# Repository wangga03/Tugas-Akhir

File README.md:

## Untuk push ke github :
1. $ git add .
2. $ git commit -m "<ini_pesan>"
3. $ git push

## Membuat branch baru (jika perlu)
$ git branch <nama_branch> : 
## pindah branch
$ git checkout <nama_baranch>

## Merge
### Misal kita ingin merge " wgg -> main " :
1. pergi ke main dulu : $ git checkout main
2. baru jalankan : $ git merge wgg
3. kemudian jalankan : $ git push

### Untuk cek sedang berada di branch mana :
$ git status
### kemudian akan muncul output :
On branch main
Your branch is up to date with 'origin/main'.

nothing to commit, working tree clean

berarti sedang berada di branch main

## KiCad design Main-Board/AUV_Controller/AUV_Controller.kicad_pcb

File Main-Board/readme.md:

Berisi tentang board unbtuk AUV
Halo test branch

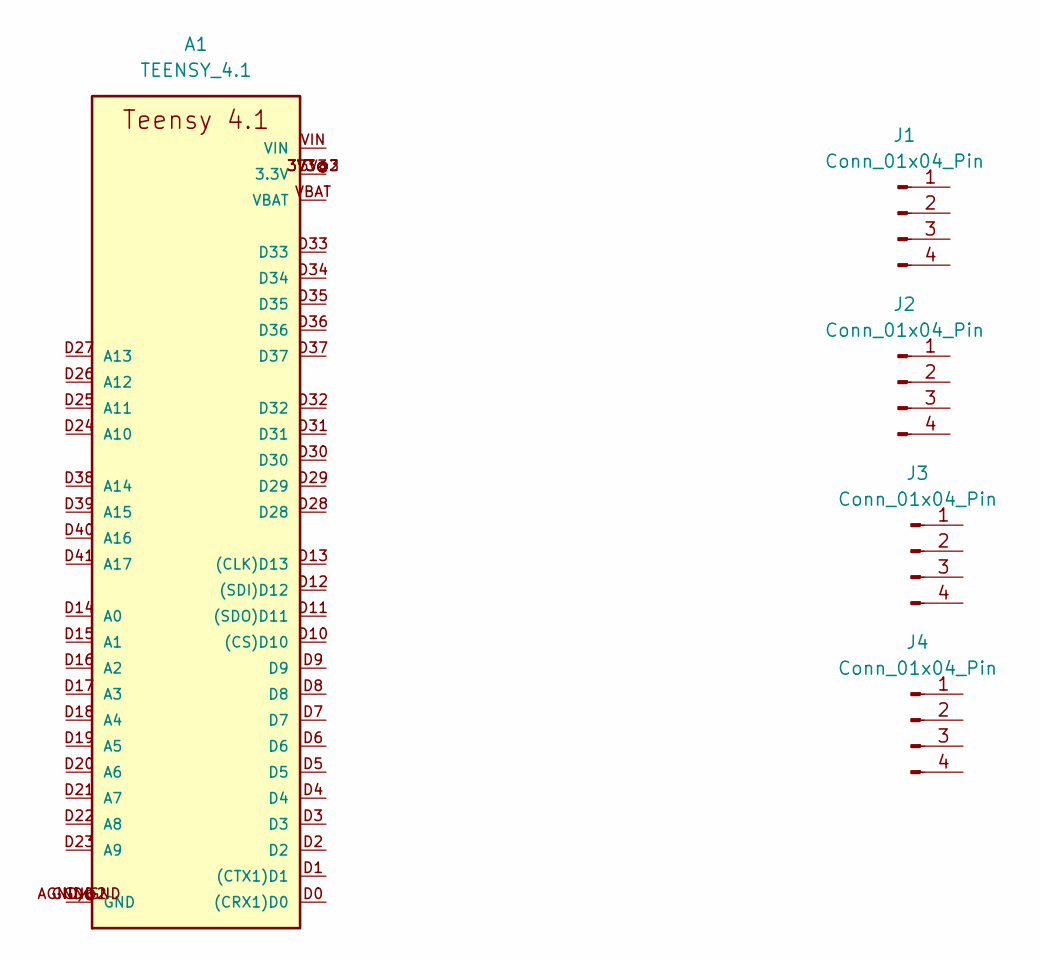
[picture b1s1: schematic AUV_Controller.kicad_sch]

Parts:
A1: TEENSY_4.1; TEENSY_LONG_EXT
J1, J2, J3, J4: Conn_01x04_Pin; JST_EH_S4B-EH_1x04_P2.50mm_Horizontal

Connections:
unnamed: A1.3V3 (3.3V), A1.3V3@2 (3.3V), A1.3V3@3 (3.3V)
unnamed: A1.AGND/GND (GND), A1.GND, A1.GND@2 (GND)

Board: 2 copper layers, 5 parts (0 on the bottom side), 2 nets, no tracks yet.

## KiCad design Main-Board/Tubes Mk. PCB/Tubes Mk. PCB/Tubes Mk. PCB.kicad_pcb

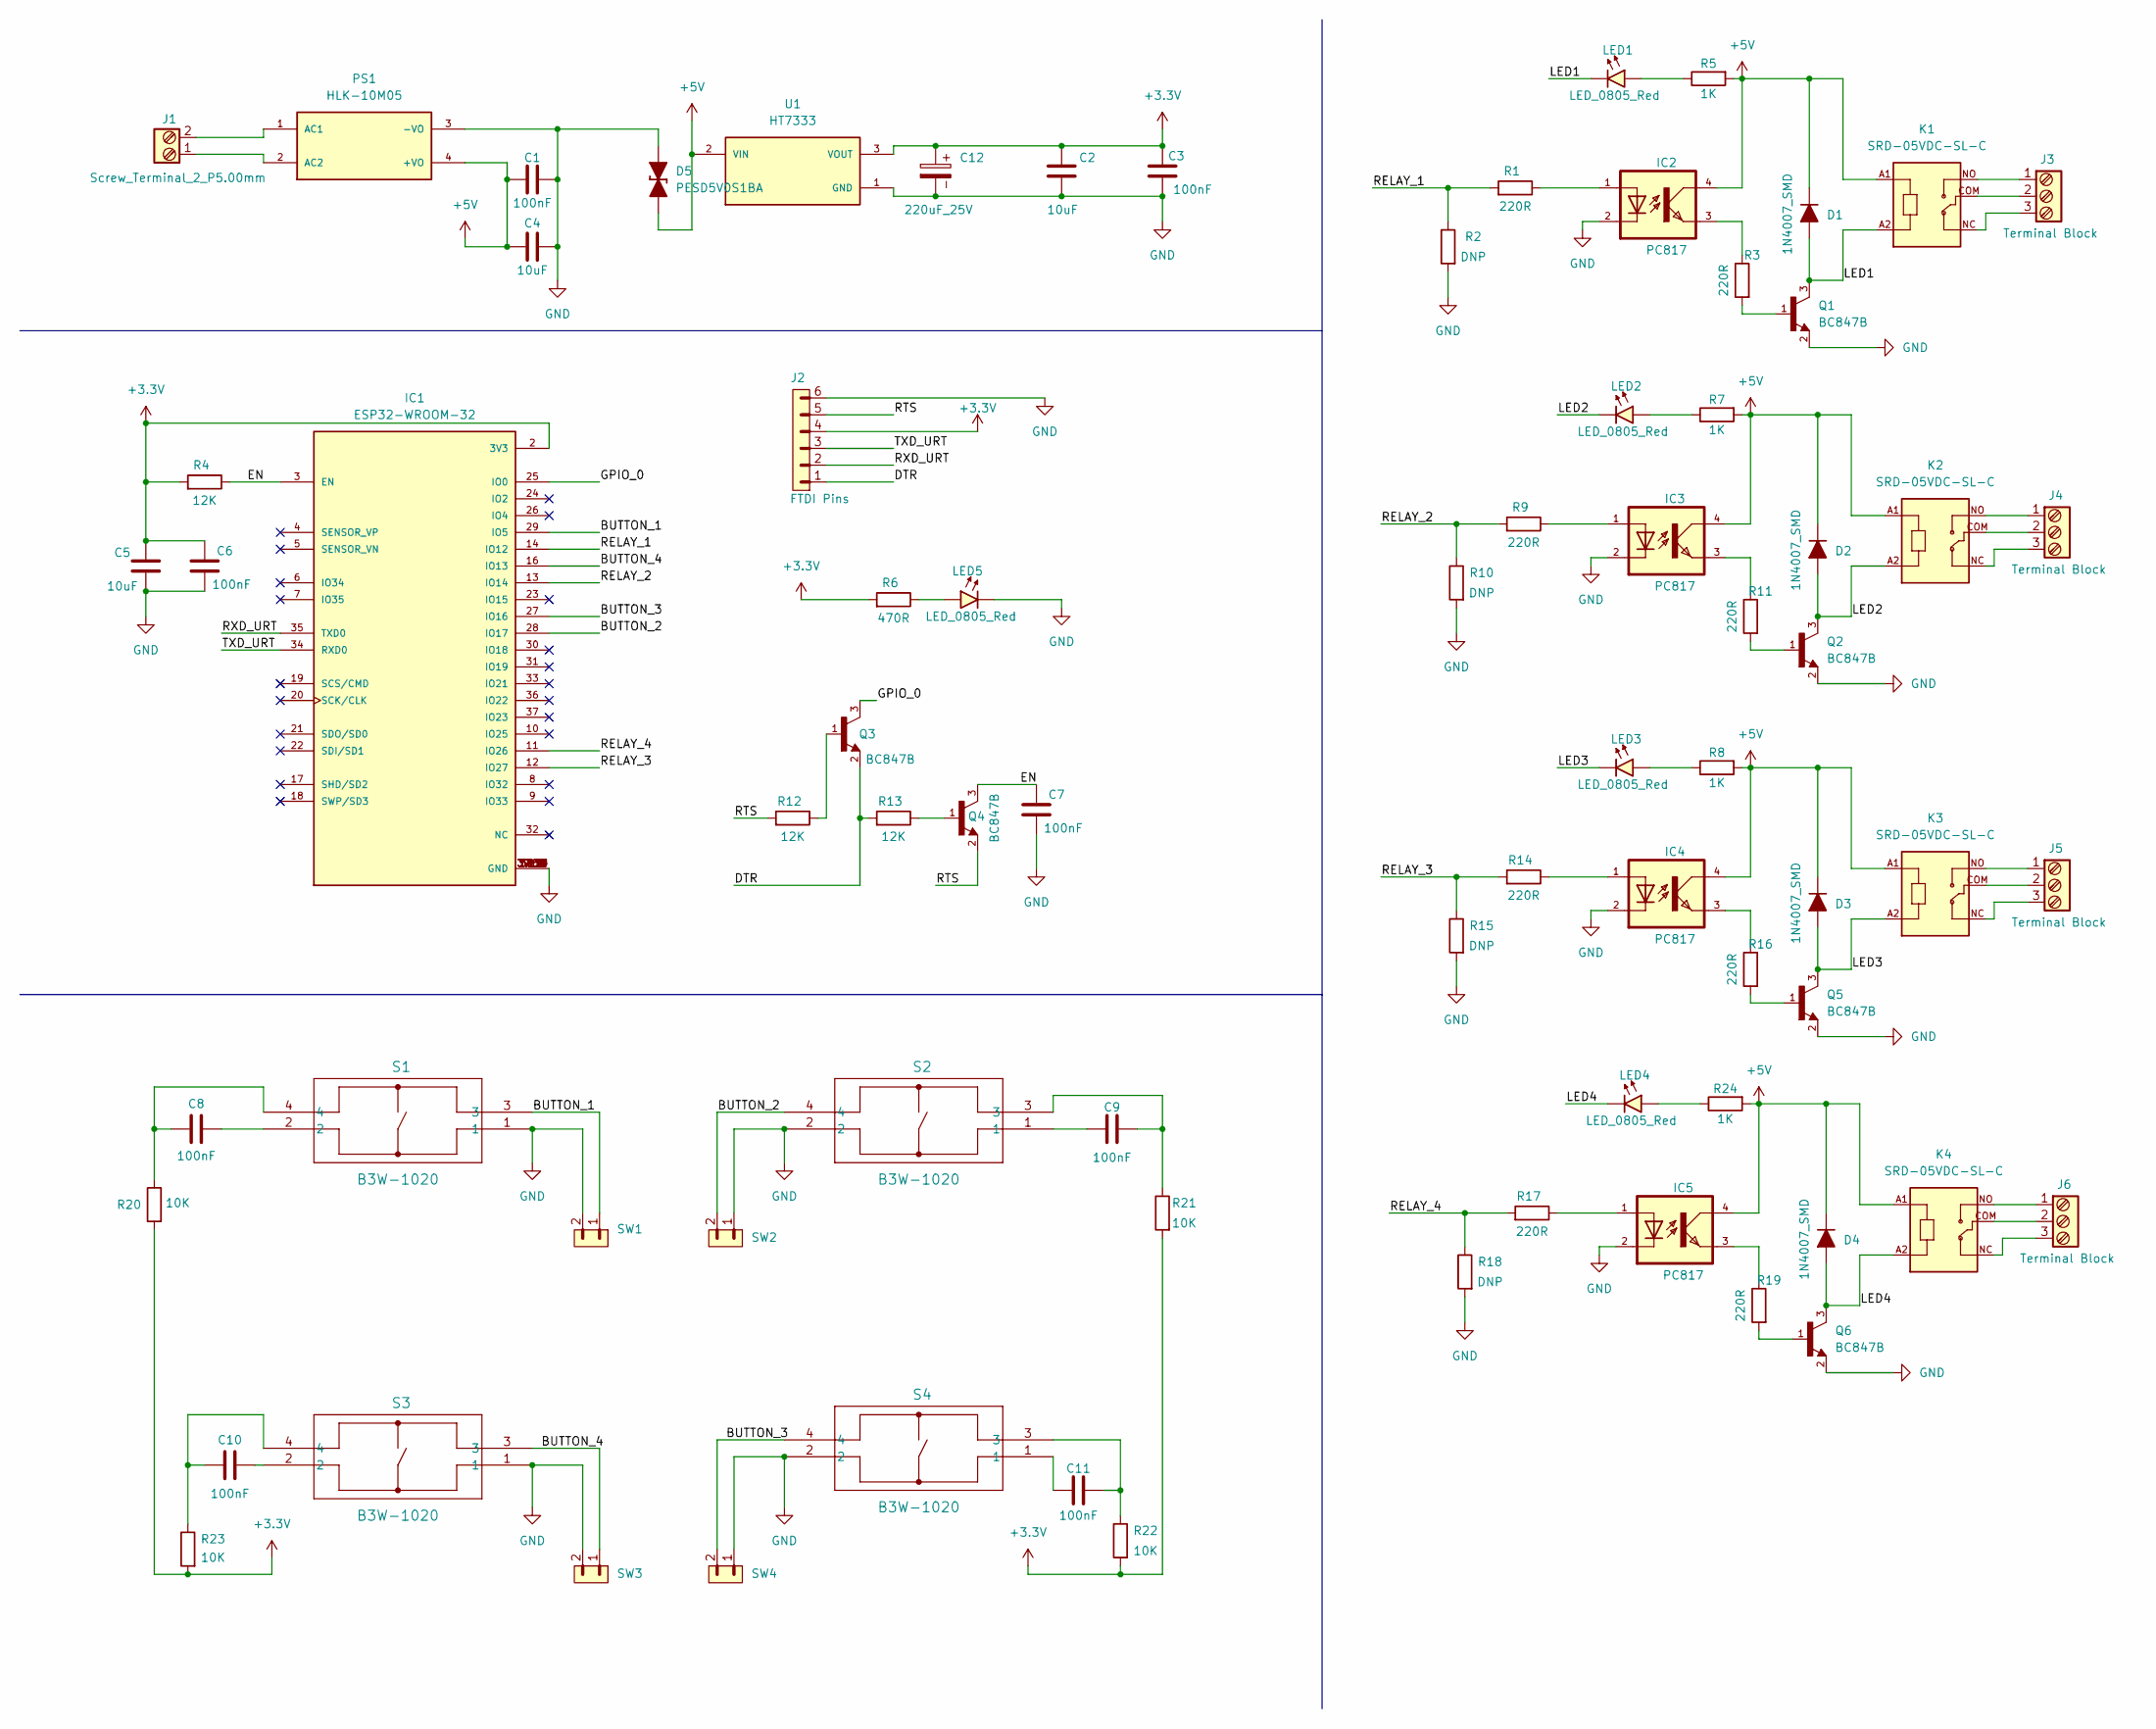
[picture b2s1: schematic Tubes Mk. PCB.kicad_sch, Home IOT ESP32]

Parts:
C1, C3, C6, C7, C8, C9, C10, C11: 100nF; C_0805_2012Metric
C2, C4, C5: 10uF; C_0805_2012Metric
C12: 220uF_25V; CP_Radial_D8.0mm_P3.50mm
D1, D2, D3, D4: 1N4007_SMD; D_SMA
D5: PESD5V0S1BA; D_SOD-323_TVS
IC1: ESP32-WROOM-32; MODULE_ESP32-WROOM-32; PARTREV 2.9
IC2, IC3, IC4, IC5: PC817; DIL04; MPN PC817X4J000F
J1: Screw_Terminal_2_P5.00mm; TerminalBlock_Phoenix_PT-1,5-2-5.0-H_1x02_P5.00mm_Horizontal
J2: FTDI Pins; PinHeader_1x06_P2.54mm_Vertical
J3, J4, J5, J6: Terminal Block; TerminalBlock_Phoenix_PT-1,5-3-5.0-H_1x03_P5.00mm_Horizontal
K1, K2, K3, K4: SRD-05VDC-SL-C; RELAY_SRD-05VDC-SL-C
LED1, LED2, LED3, LED4, LED5: LED_0805_Red; LED_0805_2012Metric
PS1: HLK-10M05; CONV_HLK-10M05; PARTREV V1.8
Q1, Q2, Q3, Q4, Q5, Q6: BC847B; SOT100P230X110-3N; PARTREV June 2002
R1, R3, R9, R11, R14, R16, R17, R19: 220R; R_0805_2012Metric
R2, R10, R15, R18: DNP; R_0805_2012Metric
R4, R12, R13: 12K; R_0805_2012Metric
R5, R7, R8, R24: 1K; R_0805_2012Metric
R6: 470R; R_0805_2012Metric
R20, R21, R22, R23: 10K; R_0805_2012Metric
S1, S2, S3, S4: B3W-1020; SW_B3W-1020_OMR
SW1, SW2, SW3, SW4: PINHD_1x2_Male; PinHeader_1x02_P2.54mm_Vertical
U1: HT7333; IC_HT7333; PARTREV 1.80

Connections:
+3.3V: C2.1, C3.1, C5.1, C6.1, C12.1, IC1.2 (3V3), J2.4, R4.1, R6.1, R20.1, R21.1, R22.1, R23.1, U1.3 (VOUT)
+5V: C1.1, C4.1, D1.1 (K), D2.1 (K), D3.1 (K), D4.1 (K), D5.1 (K), IC2.4, IC3.4, IC4.4, IC5.4, K1.A1, K2.A1, K3.A1, K4.A1, PS1.4 (+VO), R5.1, R7.1, R8.1, R24.1, U1.2 (VIN)
/BUTTON_1: IC1.29 (IO5), S1.3, SW1.1
/BUTTON_2: IC1.28 (IO17), S2.4, SW2.2
/BUTTON_3: IC1.27 (IO16), S4.4, SW4.2
/BUTTON_4: IC1.16 (IO13), S3.3, SW3.1
/DTR: J2.1, Q3.2, R13.1
/EN: C7.1, IC1.3 (EN), Q4.3, R4.2
/GPIO_0: IC1.25 (IO0), Q3.3
/LED1: D1.2 (A), K1.A2, LED1.1 (K), Q1.3
/LED2: D2.2 (A), K2.A2, LED2.1 (K), Q2.3
/LED3: D3.2 (A), K3.A2, LED3.1 (K), Q5.3
/LED4: D4.2 (A), K4.A2, LED4.1 (K), Q6.3
/RELAY_1: IC1.14 (IO12), R1.1, R2.2
/RELAY_2: IC1.13 (IO14), R9.1, R10.2
/RELAY_3: IC1.12 (IO27), R14.1, R15.2
/RELAY_4: IC1.11 (IO26), R17.1, R18.2
/RTS: J2.5, Q4.2, R12.1
/RXD_URT: IC1.35 (TXD0), J2.2
/TXD_URT: IC1.34 (RXD0), J2.3
GND: C1.2, C2.2, C3.2, C4.2, C5.2, C6.2, C7.2, C12.2, D5.2 (A), IC1.1 (GND), IC1.15 (GND), IC1.38 (GND), IC1.39_1 (GND), IC1.39_2 (GND), IC1.39_3 (GND), IC1.39_4 (GND), IC1.39_5 (GND), IC1.39_6 (GND), IC1.39_7 (GND), IC1.39_8 (GND), IC1.39_9 (GND), IC1.39_10 (GND), IC1.39_11 (GND), IC1.39_12 (GND), IC1.39_13 (GND), IC1.39_14 (GND), IC1.39_15 (GND), IC1.39_16 (GND), IC1.39_17 (GND), IC1.39_18 (GND), IC1.39_19 (GND), IC1.39_20 (GND), IC1.39_21 (GND), IC2.2, IC3.2, IC4.2, IC5.2, J2.6, LED5.1 (K), PS1.3 (-VO), Q1.2, Q2.2, Q5.2, Q6.2, R2.1, R10.1, R15.1, R18.1, S1.1, S2.2, S3.1, S4.2, SW1.2, SW2.1, SW3.2, SW4.1, U1.1 (GND)
unnamed: C8.1, S1.2
unnamed: C8.2, R20.2, S1.4
unnamed: C9.1, S2.1
unnamed: C9.2, R21.2, S2.3
unnamed: C10.1, S3.2
unnamed: C10.2, R23.2, S3.4
unnamed: C11.1, S4.1
unnamed: C11.2, R22.2, S4.3
unnamed: IC2.1, R1.2
unnamed: IC2.3, R3.2
unnamed: IC3.1, R9.2
unnamed: IC3.3, R11.2
unnamed: IC4.1, R14.2
unnamed: IC4.3, R16.2
unnamed: IC5.1, R17.2
unnamed: IC5.3, R19.2
unnamed: J3.1, K1.NO
unnamed: J3.2, K1.COM
unnamed: J3.3, K1.NC
unnamed: J4.1, K2.NO
unnamed: J4.2, K2.COM
unnamed: J4.3, K2.NC
unnamed: J5.1, K3.NO
unnamed: J5.2, K3.COM
unnamed: J5.3, K3.NC
unnamed: J6.1, K4.NO
unnamed: J6.2, K4.COM
unnamed: J6.3, K4.NC
unnamed: LED1.2 (A), R5.2
unnamed: LED2.2 (A), R7.2
unnamed: LED3.2 (A), R8.2
unnamed: LED4.2 (A), R24.2
unnamed: LED5.2 (A), R6.2
unnamed: J1.2, PS1.1 (AC1)
unnamed: J1.1, PS1.2 (AC2)
unnamed: Q1.1, R3.1
unnamed: Q2.1, R11.1
unnamed: Q3.1, R12.2
unnamed: Q4.1, R13.2
unnamed: Q5.1, R16.1
unnamed: Q6.1, R19.1

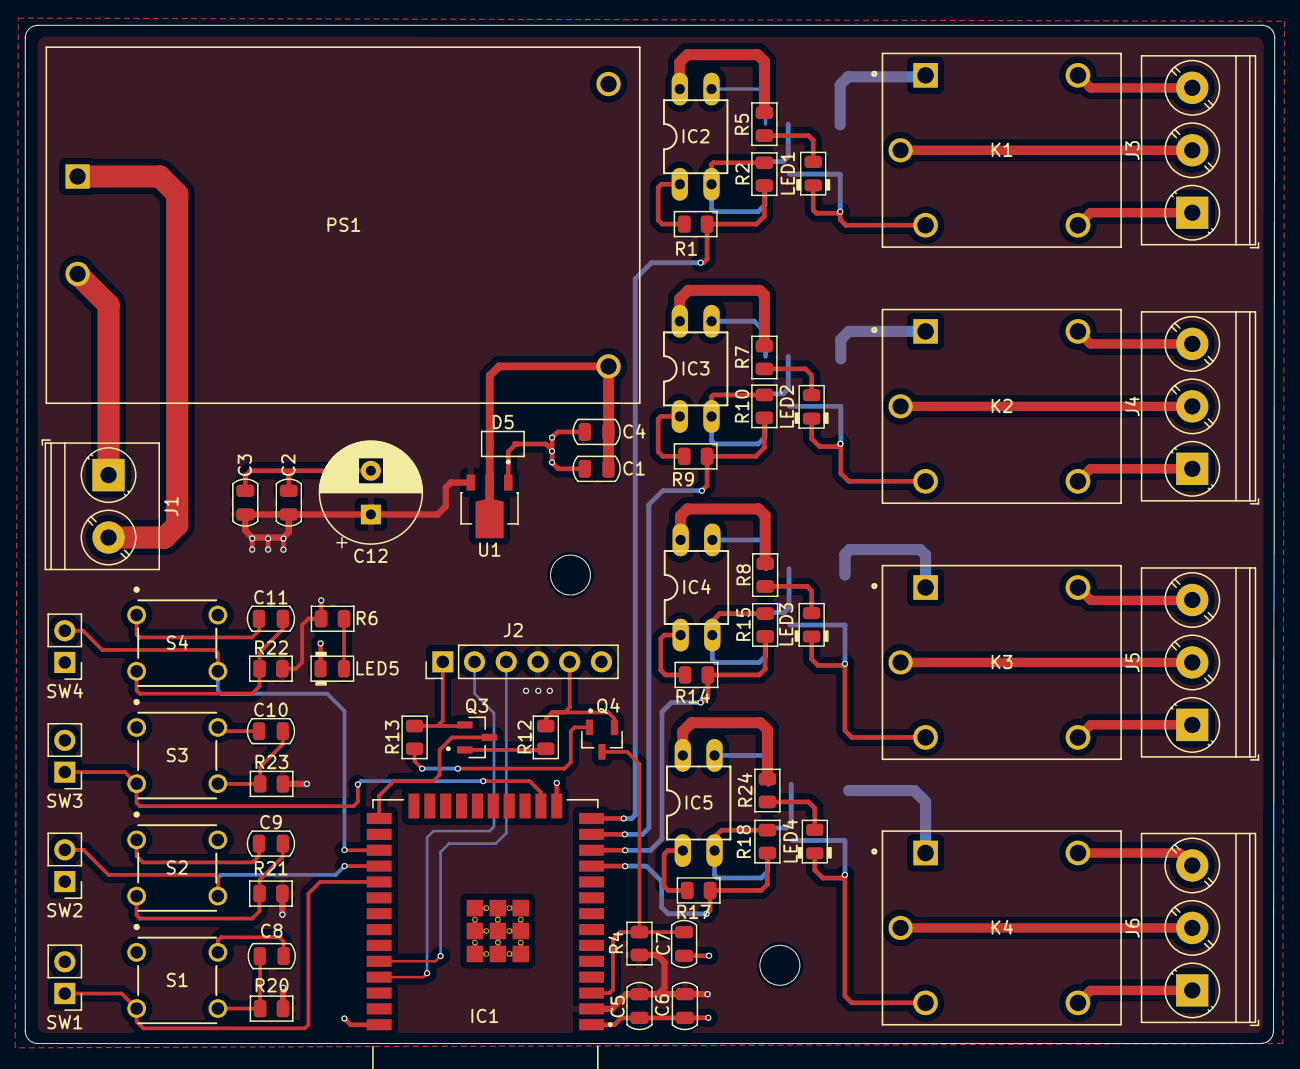
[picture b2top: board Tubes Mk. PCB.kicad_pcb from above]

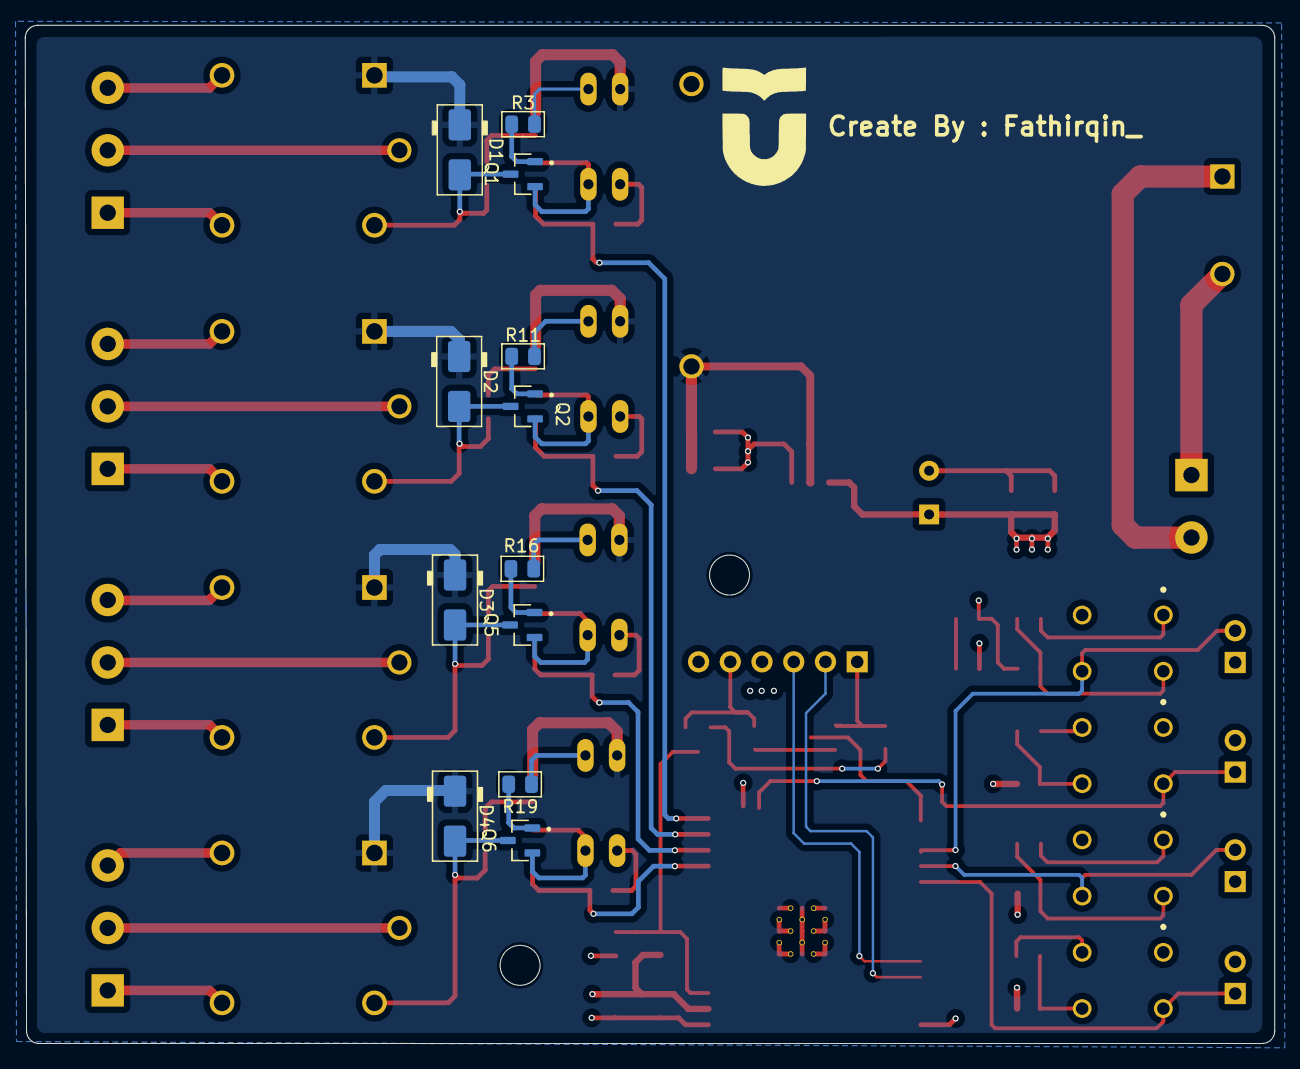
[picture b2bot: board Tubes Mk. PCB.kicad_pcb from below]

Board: 4 copper layers, 100.0 x 81.5 mm, 77 parts (12 on the bottom side), 62 nets.

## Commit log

2025-10-14 second commit
2025-10-21 halo
2025-10-21 test
2025-10-21 aksdjh
2025-10-21 shdg
2025-10-22 menambahkan projek KiCad
2025-10-22 askdhg
2025-10-22 Menambah FreeRTOS
2025-10-30 asjdh
2025-10-30 menambah board teensy pada projek
